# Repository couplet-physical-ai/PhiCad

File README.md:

# PhiCad

Describe a board and get back a routed KiCad project that has been checked by gates. PhiCad is a fork of KiCad with a design compiler, independent DRC/ERC gates, an MCP tool server and an optional AI assistant.

Created at [Exowatt](https://exowatt.com). Published under the vendor-neutral [couplet-physical-ai](https://github.com/couplet-physical-ai) organization.

## About this fork

PhiCad is a fork of [KiCad](https://www.kicad.org) ([source](https://gitlab.com/kicad/code/kicad)) maintained by couplet-physical-ai. It is not affiliated with or endorsed by the KiCad project.

- **Base:** KiCad `master` at commit `0c53452d53b0` (2026-09-01), a KiCad 11 development snapshot 3505 commits after tag `10.99.0`. Upstream history is kept unchanged. PhiCad's changes are the commits on top.
- **What PhiCad adds:**
  - the `phicad/` layer: a design-IR compiler (`phicad/synth`), the `phicad` CLI, an MCP server (`phicad/mcp`), the AI View plugin, tscircuit-based "PhiCad Verify" (`phicad/core`), parts and autoroute tooling, and docs;
  - a small set of changes to KiCad sources: Specctra DSN export and SES import jobs in `kicad-cli`, launcher and About-box changes, app display names, macOS bundle naming, and AI View plugin staging.
- **What it removes:** the upstream test and demo files that were licensed CC BY-NC-SA (see [NOTICE](NOTICE)).
- **Branding:** the application, document and launcher icons are PhiCad's own, generated from the PhiCad mark by `phicad/resources/branding/regen-icons.py`. Toolbar and menu bitmaps are KiCad's unchanged upstream artwork (credited in `resources/bitmaps_png/sources/CREDITS`).

Upstream code keeps its original licenses and notices. See [LICENSE](LICENSE), [LICENSE.README](LICENSE.README) (per-file exceptions) and [NOTICE](NOTICE).

## Status

Experimental. The `phicad/` layer has a self-contained test suite (`phicad check fast`), and CI runs it. A cold native build takes several hours, and only macOS (Apple Silicon) and Debian/Ubuntu have been exercised. Generated boards are drafts to review, not fabrication releases. There is no support commitment.

## Install

PhiCad builds from source like KiCad. The helper script installs dependencies, writes CMake presets and builds:

```bash
git clone https://github.com/couplet-physical-ai/PhiCad.git && cd PhiCad
export PATH="$PWD/phicad/bin:$PATH"
phicad bootstrap          # dependencies (macOS: Homebrew; Debian/Ubuntu: apt), one time
phicad configure dev      # build/mac-dev (macOS) or build/linux-dev (Linux)
phicad build              # ~3.5 h cold and ~16 GB RAM; ccache makes rebuilds cheap
phicad doctor             # what is missing?
```

Platform details are in [phicad/build-macos.md](phicad/build-macos.md) and [phicad/build-linux.md](phicad/build-linux.md). For the stock KiCad build documentation, see the [KiCad developer docs](https://dev-docs.kicad.org/en/build/).

## Quickstart

```bash
phicad new blinky             # a 3-part design that builds as-is
phicad build blinky.json      # place, route, pour, then run the gates (DRC, ERC, ...)
```

Every gate reports findings as data. Each finding has a stable id, a severity, the items involved, the layer, a coordinate and a suggested fix. The output is an ordinary KiCad project that you can open in PhiCad or stock KiCad.

The code-defined path builds a [tscircuit](https://github.com/tscircuit/tscircuit) `.tsx` design with the pinned engine from npm, then checks the exported board with this fork's own DRC:

```bash
cd phicad/core && bun install # pinned engine, from the committed bun.lock
phicad core capabilities
phicad core build design.tsx
```

Neither path needs network services beyond package registries. More detail:

- the [`phicad/` overview](phicad/README.md)
- the [getting-started guide](phicad/docs-site/docs/guides/getting-started.md)
- the [design IR and gates](phicad/synth/README.md)
- the [MCP tools](phicad/mcp/README.md)

## Configuration

Everything works offline by default. The optional integrations are:

| Variable | Default | Effect |
| --- | --- | --- |
| `PHICAD_LLM_GATEWAY` | *(unset: live model features disabled)* | Base URL of an OpenAI/LiteLLM-compatible gateway, used by `phicad models list/check` |
| `PHICAD_LLM_PROVIDER` | `gateway` | The `phi` provider id that holds your login for that gateway |
| `PHICAD_REPO`, `PHICAD_BUILD`, `PHICAD_VENV`, `PHICAD_KICAD_CLI` | the checkout / `build/<preset>` | Separate source and build trees for MCP/automation |
| `PHICAD_INFLUX_URL`, `PHICAD_INFLUX_ORG`, ... | *(unset: nothing shipped)* | Optional telemetry shipping. Telemetry is local-file only unless configured. See [phicad/pylib/TELEMETRY.md](phicad/pylib/TELEMETRY.md) |

The AI View assistant and the agent definitions in `phicad/agents/` run through the `phi` CLI and your own model provider. Agent `model:` refs use the provider id `gateway/<alias>`. Retarget them to your provider with `phicad models retarget`.

## Prerequisites

The KiCad build dependencies are wxWidgets, OpenCascade, ngspice, Boost, Python and the rest; `phicad bootstrap` installs them. Optional tools include Freerouting (autoroute), JLC2KiCadLib (parts fetch), Bun and Node.js 22+ (`phicad/core`), and `phi` (AI features). These are invoked as separate programs and are not bundled.

3Dconnexion SpaceMouse support uses the 3DxWare SDK headers in `thirdparty/3dxware_sdk/`. 3Dconnexion distributes these headers under GPL-3.0-or-later, as stated in each file header. On Windows and macOS the 3Dconnexion driver (navlib) is loaded dynamically if it is installed, and it is not required.

## License

GPL-3.0-or-later, the same as KiCad. See [LICENSE](LICENSE) and the per-file exceptions in [LICENSE.README](LICENSE.README). PhiCad's changes to KiCad and the `phicad/` tooling are distributed under the same terms. KiCad is a trademark of the KiCad project. See [NOTICE](NOTICE) for attribution.

## Contributing

See [CONTRIBUTING](https://github.com/couplet-physical-ai/.github/blob/main/CONTRIBUTING.md). Contributions require a DCO sign-off (`git commit -s`), and there is no CLA. Fork-specific work belongs under `phicad/`. Fixes to KiCad itself should go [upstream](https://dev-docs.kicad.org/en/contribute/).

## Security

Report vulnerabilities privately through [GitHub private vulnerability reporting](https://github.com/couplet-physical-ai/PhiCad/security/advisories/new) or by email to software@exowatt.com. Do not open a public issue. See the [security policy](https://github.com/couplet-physical-ai/.github/blob/main/SECURITY.md).

---

## Upstream KiCad README

The text below is KiCad's upstream README, kept for its credits and pointers.

For specific documentation about [building KiCad](https://dev-docs.kicad.org/en/build/), policies
and guidelines, and source code documentation see the
[Developer Documentation](https://dev-docs.kicad.org) website.

You may also take a look into the [Wiki](https://gitlab.com/kicad/code/kicad/-/wikis/home),
the [contribution guide](https://dev-docs.kicad.org/en/contribute/).

For general information about KiCad and information about contributing to the documentation and
libraries, see our [Website](https://kicad.org/) and our [Forum](https://forum.kicad.info/).

## Files
* [AUTHORS.txt](AUTHORS.txt) - The authors, contributors, document writers and translators list
* [CMakeLists.txt](CMakeLists.txt) - Main CMAKE build tool script
* [copyright.h](copyright.h) - A very short copy of the GNU General Public License to be included in new source files
* [Doxyfile](Doxyfile) - Doxygen config file for KiCad
* [INSTALL.txt](INSTALL.txt) - The release (binary) installation instructions
* [uncrustify.cfg](uncrustify.cfg) - Uncrustify config file for uncrustify sources formatting tool
* [_clang-format](_clang-format) - clang config file for clang-format sources formatting tool

## Subdirectories

* [3d-viewer](3d-viewer)         - Sourcecode of the 3D viewer
* [bitmap2component](bitmap2component)  - Sourcecode of the bitmap to PCB artwork converter
* [cmake](cmake)      - Modules for the CMAKE build tool
* [common](common)            - Sourcecode of the common library
* [cvpcb](cvpcb)             - Sourcecode of the CvPCB tool
* [demos](demos)             - Some demo examples
* [doxygen](doxygen)     - Configuration for generating pretty doxygen manual of the codebase
* [eeschema](eeschema)          - Sourcecode of the schematic editor
* [gerbview](gerbview)          - Sourcecode of the gerber viewer
* [include](include)           - Interfaces to the common library
* [kicad](kicad)             - Sourcecode of the project manager
* [libs](libs)           - Sourcecode of KiCad utilities (geometry and others)
* [pagelayout_editor](pagelayout_editor) - Sourcecode of the pagelayout editor
* [patches](patches)           - Collection of patches for external dependencies
* [pcbnew](pcbnew)           - Sourcecode of the printed circuit board editor
* [phicad](phicad)           - PhiCad's fork layer (not part of upstream KiCad)
* [plugins](plugins)           - Sourcecode for the 3D viewer plugins
* [qa](qa)                - Unit testing framework for KiCad
* [resources](resources)         - Packaging resources such as bitmaps and operating system specific files
    - [bitmaps_png](resources/bitmaps_png)       - Menu and program icons
    - [project_template](resources/project_template)          - Project template
* [thirdparty](thirdparty)           - Sourcecode of external libraries used in KiCad but not written by the KiCad team
* [tools](tools)             - Helpers for developing, testing and building
* [translation](translation) - Translation data files (managed through [Weblate](https://hosted.weblate.org/projects/kicad/master-source/) for most languages)
* [utils](utils)             - Small utils for KiCad, e.g. IDF, STEP, and OGL tools and converters

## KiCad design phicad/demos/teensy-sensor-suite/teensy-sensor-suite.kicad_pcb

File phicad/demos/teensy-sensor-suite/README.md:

# Teensy 4.0 Prototyping Sensor Suite — PhiCad demo board

A generated, openable 2-layer carrier board for prototyping an I²C sensor suite on a
Teensy 4.0. It exists to exercise the fork end to end: it is written as s-expressions by
a script, opened by `kicad-cli`, DRC'd, rendered, exported to gerbers/STEP, and read back
over the IPC API by an agent.

## The design

| Ref | Part | Role |
| --- | --- | --- |
| J1, J2 | 1×14 2.54 mm headers, 15.24 mm (0.6 in) row pitch | Teensy 4.0 sockets |
| U2 | Bosch LGA-8 (`LSM6DSO`) | IMU on the I²C bus |
| U3 | Bosch LGA-8 (`BME280`) | environmental sensor on the I²C bus |
| R1, R2 | 4k7 0805 | SDA / SCL pull-ups to 3V3 |
| C1, C2 | 100 nF 0805 | per-sensor decoupling |
| C3 | 10 µF 0805 | 3V3 bulk |
| D1, R3 | LED 0805 + 1k | status LED on a spare GPIO |
| J3, J4 | 1×4 headers | I²C sensor breakouts (GND / 3V3 / SDA / SCL) |
| J5 | 1×5 header | SPI breakout (GND / SCK / MOSI / MISO / CS) |
| H1–H4 | 3.2 mm | M3 mounting holes |

Signals follow the real Teensy 4.0 pinout: I²C on pins 18/19 (SDA/SCL), SPI on 11/12/13
with CS on 10. Board is 50 × 43 mm with chamfered corners, a `GND` pour on B.Cu, and
3V3 + I²C routed on F.Cu.

## Regenerating

```bash
build/venv/bin/python phicad/demos/teensy-sensor-suite/generate_board.py
# or write elsewhere:
build/venv/bin/python phicad/demos/teensy-sensor-suite/generate_board.py -o /tmp/scratch
```

Output is deterministic — UUIDs are `uuid5` of a stable namespace, so regenerating an
unchanged design produces a byte-identical file and `git diff` shows only real changes.
Footprints come from the stock libraries under
`~/Library/Application Support/kicad/stock/footprints/`.

## Three fork-specific syntax facts

Verified against a board **written by this fork**, not assumed from upstream 10.0:

1. Placement is `(transform (translate X Y) (rotate A) (scale 1 1))`, not `(at x y rot)`.
2. A pad's `(at …)` is its **local, unrotated** offset from the footprint origin; the
   footprint's `(rotate …)` applies on top, so pad coordinates don't change when a part
   is rotated.
3. Nets are referenced **by name only** — this fork writes no numeric `(net N "name")`
   table. A net exists purely by being named on a pad, segment or zone.

To re-derive them: copy a fixture to `/tmp`, open **and save** it through the fork
(saving is what rewrites a board to version `20260831`; opening alone does not modify
it), then read the result.

## Checking it: `check_routing.py`

DRC is the authority, but it costs ~25 s and reports violations in board coordinates that
are tedious to trace back to the generator's intent. `check_routing.py` reads the emitted
board and answers the same questions in **0.07 s** — 350× faster — in the generator's own
vocabulary:

```bash
python3 check_routing.py            # exit 0 = clean, 1 = problems
```

It checks, in the generator's own vocabulary:

| Check | Catches |
| --- | --- |
| track-to-track clearance, per layer, between different nets | shorts and crossings |
| tracks through holes they don't own (skipping the pad's own net) | a lane run through a header pin |
| refdes overlapping pads or another refdes | `silk_over_copper`, `silk_overlap` |
| zone outline vs the board edge | a pour overhanging the chamfers |
| track endpoints and pads vs the board edge | a drop column that walked off the board |
| more than one track width on a single net | a call site that forgot to pass one |
| zero-length segments | dangling stubs |

For clearance failures it prints the worst offenders with coordinates and net names, which
is what makes a fix obvious rather than guesswork.

Every one of those checks except the first two was added **after** the corresponding bug had
already shipped past the others, so each is a regression test as much as a check. Each was
also verified by deliberately reintroducing its bug in a throwaway fixture and confirming it
fires — a check that has never failed on purpose is not known to work.

Run it after every generator edit; run DRC once it is clean. This loop is what took the
routing from 32 conflicting net pairs to zero.

## How long does prompt → PCB take?

Two very different numbers, and conflating them is how "AI designs a PCB in seconds" claims
get made.

**Regenerating this board: 0.21 s**, measured end to end — edit a constant, emit the
`.kicad_pcb`, run the full geometric check, and produce a PNG you can look at:

| Step | Time |
| --- | --- |
| `generate_board.py` (18 footprints, 101 segments, 35 vias, 27 nets, 4305 lines) | **0.02 s** |
| `check_routing.py` (seven checks: clearance, holes, silk, zone, edge, widths, dangling) | **0.16 s** |
| `plot_board.py` → SVG + PNG | **0.12 s** |
| whole loop | **0.41 s** |

For comparison `kicad-cli pcb drc` is ~25 s, so the fast loop is roughly **350×** quicker.
That ratio is the entire reason this board got to zero violations: it makes a wrong guess
cost a fifth of a second instead of half a minute.

**Designing it the first time: about 2 hours of agent work**, in six commits (18:23 → 20:13
on 2026-09-02), and it was not one prompt — it was a feedback loop:

| | |
| --- | --- |
| first board that opened and exported | ~25 min, **46 DRC violations** |
| routing rebuilt on a declared corridor/lane plan | conflicting net pairs 32 → **0** |
| silkscreen placed per part instead of a fixed offset | 15 warnings → **0** |
| real DRC run after the checker said CLEAN | **26 errors** → 0 (5 further commits) |
| last 4 advisory warnings fixed, not downgraded | 4 → **0** |
| J5 orientation + SPI approach fixed | found only by **plotting and looking at it** |

So the honest answer: **a change to an existing board is sub-second; a new board is hours,
and most of that is iteration, not generation.** The generator is fast; getting the design
*right* is the work. What the tooling buys is that each iteration is 0.2 s instead of 25 s.

One lesson worth keeping: the numeric checks all passed while J5 sat with its pads off the
bottom edge of the board and its SPI tracks landing on bare laminate. **A picture caught
what four checks missed** — which is why `plot_board.py` exists and why it is part of the
loop rather than an afterthought. Looking at the rendered board then found three more faults
in a row that no check modelled: a ground pour overhanging the chamfers, the 3V3 drop column
sitting on the west board edge, and two I2C trunks silently wider than their own taps. Each
is now a check, but the render is what found them.

The corollary is uncomfortable and worth stating: **"CLEAN" only ever means "none of the
things I thought to measure".** Every check in the table above was added after its bug had
already passed all the earlier ones.

## Verifying: `./verify.sh`

One command runs everything: regenerate, determinism check, `check_routing.py`, DRC,
both renders, and all four exports, then prints a PASS/FAIL table.

```bash
./verify.sh          # full run
./verify.sh -q       # summary only
```

Before doing any work it checks two things that otherwise masquerade as a broken board:

1. **Directory services.** If `opendirectoryd` is wedged, *every* `kicad-cli` invocation
   aborts with `Abort trap: 6` / exit 134 and **no message at all** — identical to a corrupt
   board. The script tests `dscl` first and tells you to `sudo killall opendirectoryd`.
   (Other symptoms of the same fault: `sysmond service not found`, `ps ax` truncating, DNS
   failing. The tell in the unified log is `mbr_check_membership_ext(): Input/output error`.)
2. **Stale kifaces.** If `libkicommon`/`libkigal` were rebuilt but `_pcbnew.kiface` was not
   relinked, board loading aborts the same way. The script relinks if ninja reports pending
   steps.

Both were hit while building this demo, and both cost real time because the failure mode is
a silent 134 with no output. Rule the environment out before debugging the board.

## Verification status

| Check | Result |
| --- | --- |
| `check_routing.py` | **CLEAN** — 0 clearance/short pairs, 0 hole violations, 0 silk overlaps, 101 segments |
| `plot_board.py` (no kicad-cli needed) | `plot-current.png` — renders the **current** revision |
| silkscreen placement | all 18 refdes clear their nearest pad (min gap 0.38 mm) and each sits by its own part |
| regenerate twice | byte-identical (`md5` match) — deterministic |
| s-expression integrity | balanced parens; 18 footprints, 96 segments, 35 vias, 1 zone |
| `kicad-cli pcb drc --refill-zones` | **0 errors, 0 warnings, 0 unconnected** |
| `kicad-cli pcb render` top + bottom | OK (see `render-top.png`, `render-bottom.png`) |
| `kicad-cli pcb export svg` / gerbers / step | OK — 21 gerber files |
| read back over IPC (`session_inspect.py`) | 18 footprints, 75 pads, 27 nets, 106 tracks, 35 vias, 1 zone |

> **Re-measured 2026-09-03 after a reboot, and now fully clean.** Every row above is from
> the current revision: `./verify.sh` passes all ten steps, and DRC reports
> **0 errors, 0 warnings and 0 unconnected items** -- the board is fully routed.
>
> An earlier version of this note claimed the 10 unconnected items were deliberate
> (`J2.VIN` with no consumer, `J3/J4.GND` returning through the pour). **That was wrong, and
> wrong in a way worth recording:** the actual 10 were the spare VDD and GND pads of the two
> LGA-8 sensors, which the router never touched. A floating VDD pad is a real defect -- the
> die bonds to all of them, so leaving one open puts the supply through a single bond wire
> and defeats the decoupling. They are now bonded (see `bond_power_pads`). Do not describe
> an unconnected item as intentional without reading the DRC item list.
>
> The earlier caveat here said these numbers were unverified because `kicad-cli` aborted on
> every board-loading command. That was chased to a root cause and it was **not** a board or
> fork defect: **`opendirectoryd` had died**, so `kicad-cli` aborted with SIGABRT while
> resolving the user at startup. Two corrections to what that caveat used to claim:
>
> * `kicad-cli version` does **not** keep working. The wedge degrades; by the second
>   occurrence even `version` aborted. Do not use it as an "environment is fine" probe.
> * `sudo killall opendirectoryd` is **not** a fix -- `sudo` needs the very daemon that is
>   down (`you do not exist in the passwd database`), and `launchctl kickstart` fails with
>   `141: Reentrancy avoided`. **Only a reboot works.** `verify.sh` now checks `dscl` first
>   and refuses to run rather than reporting misleading failures.

### Suppressions: 9 → 4, each removal earned

`rule_severities` started with nine downgraded checks, which is how a board reports "46
violations" and still looks acceptable. Six of the nine were **stale or simply wrong**, and
were removed once the underlying fault was measured and fixed rather than assumed cosmetic:

| Removed | Why it was safe to remove |
| --- | --- |
| `solder_mask_bridge` | tightest mask web on the board is **+0.200 mm** against a 0.100 mm limit. This one should never have been downgraded — a merged aperture between two nets shorts them in reflow. |
| `silk_over_copper`, `silk_overlap` | 0 refdes-over-pad and 0 refdes-over-refdes overlaps after `REF_POS` placed labels per part |
| `silk_edge_clearance` | every refdes box sits ≥ 0.2 mm inside the outline |
| `pth_inside_courtyard`, `npth_inside_courtyard` | 0 holes fall inside another footprint's courtyard (14 courtyards checked) |

The four that remain are structural, not cosmetic hand-waving:

| Kept | Why |
| --- | --- |
| `lib_footprint_mismatch` (ignore) | the generator strips the library Reference/Value and emits its own, so **every** footprint mismatches its library by construction |
| `footprint_type_mismatch` (ignore) | stock through-hole footprints reused for headers this board defines itself |
| `lib_footprint_issues` (warning) | belongs to the stock library, not to this board |
| `copper_sliver` (warning) | zone-fill artefact; the filler resolves it and it cannot be evaluated without running the filler |

The general rule this taught: **measure the thing, then delete the suppression.** Downgrading
a check because it is inconvenient converts a real defect into a clean-looking report.

### Honest DRC status

The board **opens, renders and exports**. The routing is geometrically clean by construction
(see the corridor plan below), and the silkscreen overlaps were **fixed rather than
suppressed** — `REF_POS` gives each part a reference-designator offset that clears its own
pads and its neighbours, which is what removed the `silk_over_copper` / `silk_overlap`
population. What remains downgraded in `rule_severities` is genuinely advisory, for the
reasons listed below.

Counts from the last successful DRC run of the previous revision (before the silk fix):

| Type | Count |
| --- | --- |
| `solder_mask_bridge` | 9 |
| `lib_footprint_mismatch` | 8 |
| `silk_over_copper` | 8 |
| `silk_overlap` | 7 |
| `shorting_items` | 3 |
| `hole_clearance` | 2 |
| `courtyards_overlap` | 2 |
| `pth_inside_courtyard` | 2 |
| `via_dangling` | 2 |
| `tracks_crossing` | 1 |
| `clearance` | 1 |
| `npth_inside_courtyard` | 1 |

What they are, and why they are left:

- **`shorting_items` / `clearance` / `tracks_crossing` (5)** — the F.Cu routing is
  hand-written centre-line geometry in the generator, so a few segments pass closer to a
  pad than the 0.2 mm clearance allows. These are the ones a real design would fix by
  routing properly (or by letting the router do it).
- **`solder_mask_bridge` (9)** — 0805 pads and 2.54 mm header pads sit close enough that
  their mask apertures merge. Normal for this geometry; fixed with a mask-expansion rule.
- **`lib_footprint_mismatch` (8)** — expected and harmless: the generator strips the
  library's `Reference`/`Value` properties and emits its own, so the board footprint is
  intentionally not byte-identical to the library original.
- **`silk_over_copper` / `silk_overlap` (15)** — stock silkscreen outlines overlapping
  pads and each other at this density. Cosmetic.
- **`hole_clearance` / `*_inside_courtyard` / `via_dangling` (7)** — stitching vias and
  courtyards near the M3 holes and header rows.

## How the routing is kept legal

The first revisions picked every track coordinate by hand and produced 20–30 crossing and
short errors, because whether two tracks collided depended on component positions that kept
moving. The generator now derives routing from three declared plans, and *nothing* picks a
coordinate by hand:

- **`CORRIDOR`** — one reserved x per F.Cu trunk (`SDA`, `SCL`, `3V3`), 2 mm apart. Power
  is deliberately on the **far side** of the sensor column from the signals, so a part's
  power tap and signal taps leave in opposite directions and never cross.
- **`LANE`** / **`DROP`** — one reserved y *and* one reserved drop column per B.Cu
  crossing, allocated from a single ordered list so sharing either is impossible by
  construction. The band clears the last header pin row by ≥ `min_hole_clearance` + pad
  radius.
- **`JOG`** — per-pad escape offsets for pads that share a row (an LGA row, a header on
  2.54 mm pitch tapping trunks 2 mm apart). Escapes leave **perpendicular** to the row and
  step sideways in proportion to the jog, so two pads escaping by different amounts also
  use different columns.

`tap()` then routes a pad to its trunk, automatically diving under any *other* trunk in the
way via `bcu_cross()`. Because it reads `CORRIDOR`, placement can change freely and the
routing stays legal.

Do not treat this board as a fabrication-ready reference — it has no schematic, and the
remaining warnings would want a real review. Treat it as proof the toolchain works on a
non-trivial design, and as a fixture for agent-driven edits.

## Bugs this demo caught

Worth recording, because each produced a *silently* wrong board rather than an error:

- Pad numbers in a `.kicad_mod` are **strings**. Passing `{1: "GND"}` matched nothing and
  left every header pin netless — the file loaded fine and looked right in a render, but
  had 28 fewer nets. Fixed by normalising keys with `str()`.
- Attaching a net after the pad's `(layers …)` line breaks on stock pads that carry
  trailing keys such as `(remove_unused_layers no)`; only the first pad got a net. The net
  is now emitted just before the pad's closing paren.
- A vertical 1×14 header already runs pin 1 → pin 14 along **+y** at rotation 0. Rotating
  it 270° laid both rows along −x, overlapping each other — which DRC reported as 8
  co-located holes rather than as a placement error.
- **A GND stub was attached to J1 pin 1, which is `T_D0` on a Teensy 4.0 — not ground.**
  The Teensy's left row has no ground pin at all; ground is on J2 pins 1 and 13. The
  geometric check surfaced this only as "a track sits exactly on a hole of another net";
  the real fault was electrical. Worth remembering that a clean geometry check does not
  imply a correct netlist.
- **Two pads of one part can be electrically equivalent but not interchangeable.** A
  BME280's pads 1 and 7 are both VDD, but pad 1 sits west of the SDA pad while the power
  trunk is east, so a tap from it had to cross SDA. No jog fixes that — the part had to be
  rotated 180° so its VDD pads face the power trunk. Rotating U3 removed the last
  clearance violations on the board.
- **`%` binds tighter than the surrounding subtraction.** `TEENSY_X - 4.0 - 1.2 * i % 5`
  collapsed four SPI lanes onto nearly the same corridor, which appeared as 20
  `tracks_crossing` errors rather than as an arithmetic mistake.

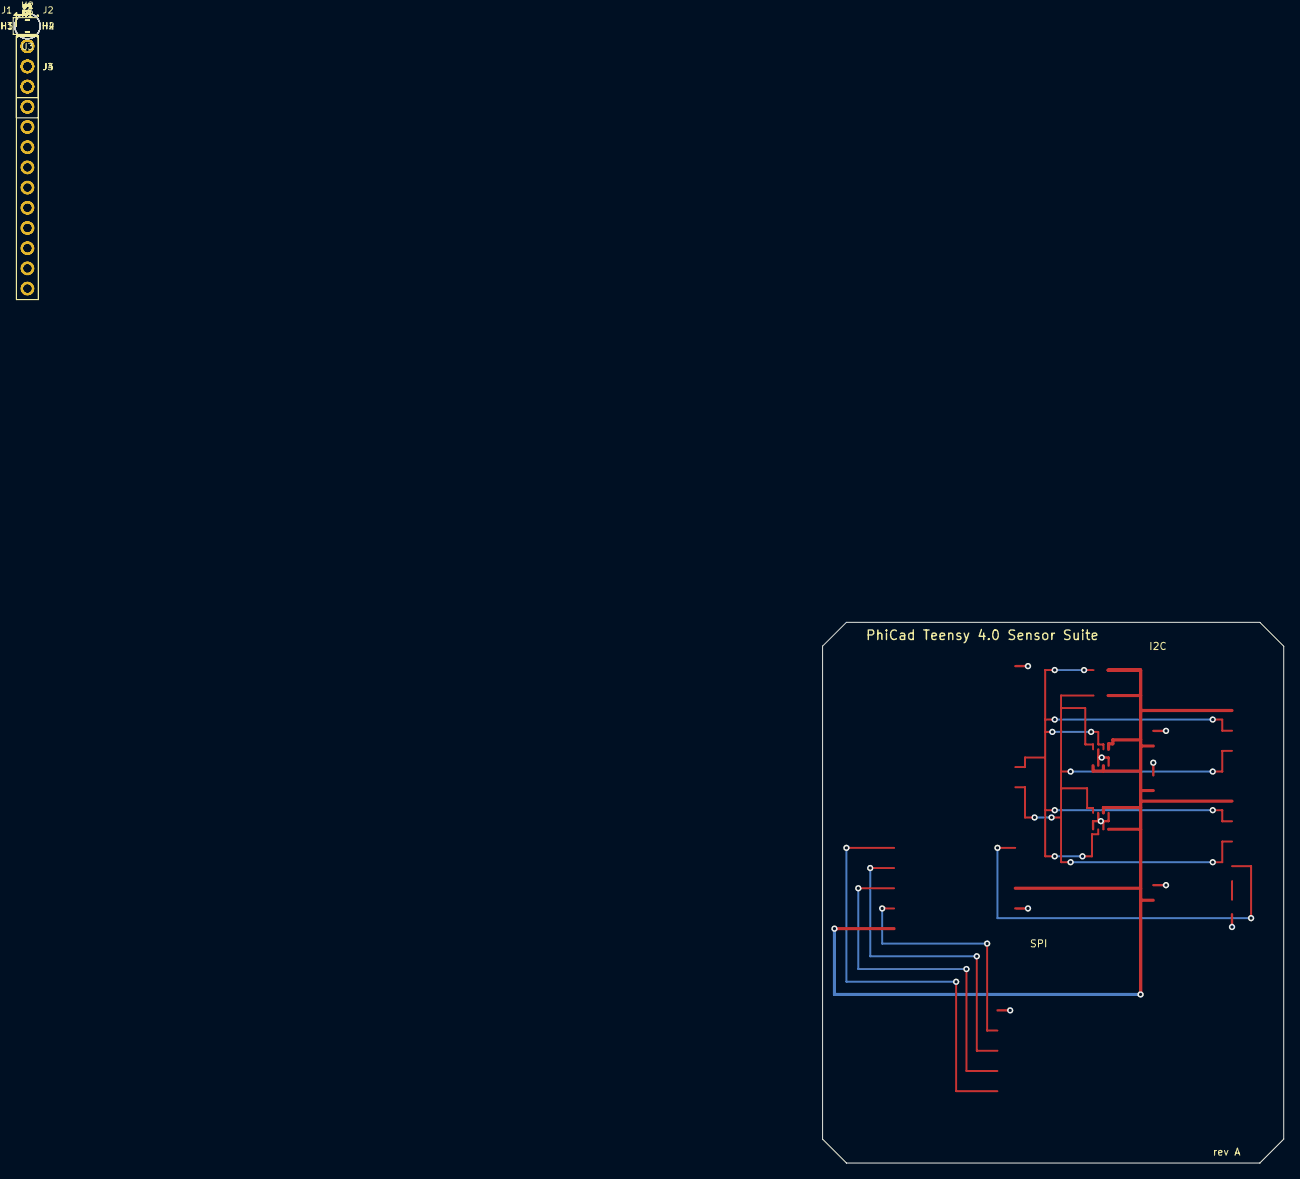
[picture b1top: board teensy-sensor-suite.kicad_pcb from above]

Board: 2 copper layers, 58.0 x 68.0 mm, 18 parts (0 on the bottom side), 10 nets.

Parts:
C1, C2: 100nF; C_0805_2012Metric
C3: 10uF; C_0805_2012Metric
D1: STATUS; LED_0805_2012Metric
H1, H2, H3, H4: M3; MountingHole_3.2mm_M3
J1: Teensy4.0-L; PinHeader_1x14_P2.54mm_Vertical
J2: Teensy4.0-R; PinHeader_1x14_P2.54mm_Vertical
J3, J4: I2C; PinHeader_1x04_P2.54mm_Vertical
J5: SPI; PinHeader_1x05_P2.54mm_Vertical
R1, R2: 4k7; R_0805_2012Metric
R3: 1k; R_0805_2012Metric
U2: LSM6DSO; Bosch_LGA-8_2.5x2.5mm_P0.65mm_ClockwisePinNumbering
U3: BME280; Bosch_LGA-8_2.5x2.5mm_P0.65mm_ClockwisePinNumbering

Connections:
3V3: C1.1, C2.1, C3.1, J1.14, J2.12, J3.2, J4.2, R1.2, R2.2, U2.4, U2.6, U2.8, U3.1, U3.7
GND: C1.2, C2.2, C3.2, J2.1, J2.13, J3.1, J4.1, J5.1, R3.1, U2.2, U2.5, U2.7, U3.2, U3.4, U3.6, U3.8
LED_A: D1.2, J2.10
LED_K: D1.1, R3.2
SCL: J2.7, J3.4, J4.4, R2.1, U2.1, U3.5
SDA: J2.6, J3.3, J4.3, R1.1, U2.3, U3.3
SPI_CS: J1.10, J5.5
SPI_MISO: J1.12, J5.4
SPI_MOSI: J1.11, J5.3
SPI_SCK: J1.13, J5.2
